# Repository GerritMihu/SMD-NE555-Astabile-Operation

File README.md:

# SMD-NE555-Astabile-Operation
 NE555 als astabile Kippstufe

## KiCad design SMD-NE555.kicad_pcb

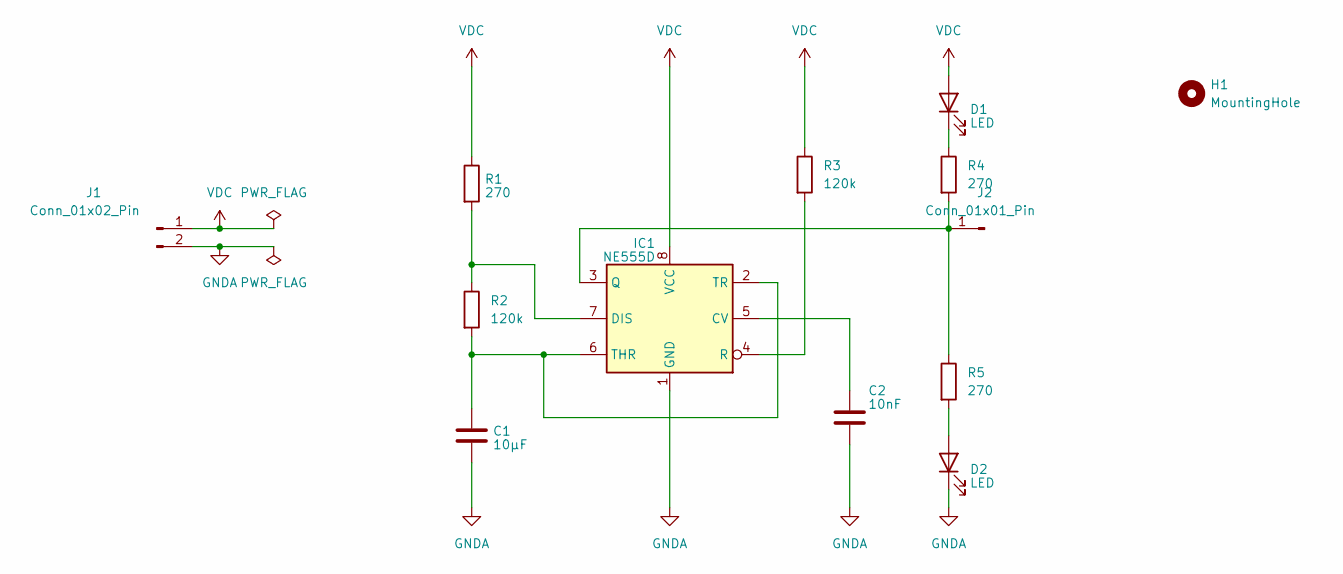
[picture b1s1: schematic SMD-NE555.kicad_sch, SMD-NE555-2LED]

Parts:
C1: 10µF; C_1206_3216Metric_Pad1.33x1.80mm_HandSolder
C2: 10nF; C_0805_2012Metric_Pad1.18x1.45mm_HandSolder
D1, D2: LED; LED_0805_2012Metric_Pad1.15x1.40mm_HandSolder
H1: MountingHole; MountingHole_2.7mm_M2.5_DIN965
IC1: NE555D; SOIC-8_3.9x4.9mm_P1.27mm
J1: Conn_01x02_Pin; PinHeader_1x02_P2.54mm_Vertical
J2: Conn_01x01_Pin; PinHeader_1x01_P2.54mm_Vertical
R1, R4, R5: 270; R_0805_2012Metric_Pad1.20x1.40mm_HandSolder
R2, R3: 120k; R_0805_2012Metric_Pad1.20x1.40mm_HandSolder

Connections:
GNDA: C1.2, C2.2, D2.1 (K), IC1.1 (GND), J1.2
unnamed: D1.1 (K), R4.1
unnamed: D2.2 (A), R5.2
unnamed: C2.1, IC1.5 (CV)
unnamed: IC1.7 (DIS), R1.2, R2.1
unnamed: IC1.3 (Q), J2.1, R4.2, R5.1
unnamed: IC1.4 (R), R3.2
unnamed: C1.1, IC1.2 (TR), IC1.6 (THR), R2.2
VDC: D1.2 (A), IC1.8 (VCC), J1.1, R1.1, R3.1

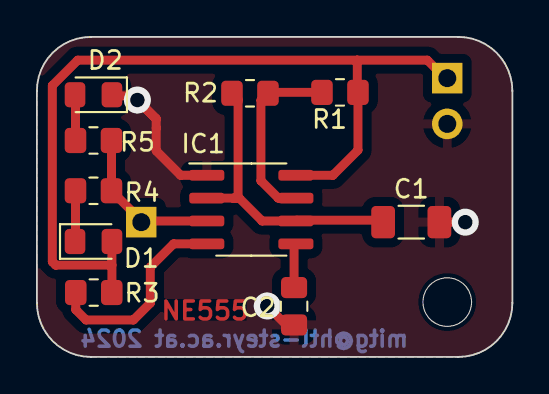
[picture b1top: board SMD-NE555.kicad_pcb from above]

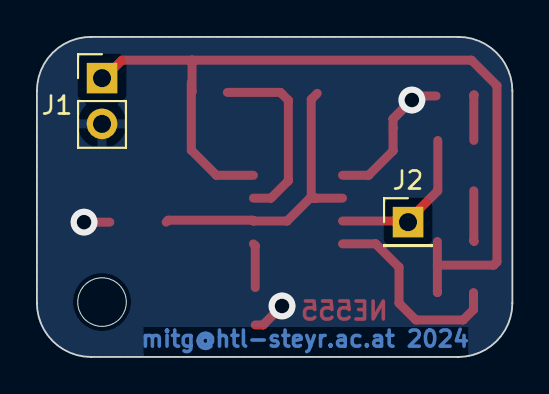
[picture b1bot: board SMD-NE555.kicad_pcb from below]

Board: 2 copper layers, 26.4 x 17.8 mm, 13 parts (2 on the bottom side), 9 nets.

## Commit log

2024-05-02 added details
2024-05-02 Added files
2024-11-20 rounded corners gnd plane top&bot
2024-11-20 erc error pwr flag
2024-11-20 new workflow
2024-11-20 molex to pinheader2.54 1x02
